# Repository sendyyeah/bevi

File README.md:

# bevi
 Inspired by Vortex Vibe and Wyvern, so here is Vibe Southpaw

## Case File

You can find acrylic sandwich case file [here](https://github.com/sendz/keyboard-case)

## License

This design may be reproduced, modified, and manufactured for **Personal Use Only** and not for **Public Sale**, however I allow to anyone who want to do small GB for their community for maximum of 10 pieces of this PCB per group buy.

)

This work is licensed under a [Creative Commons Attribution-NonCommercial 4.0 International License](http://creativecommons.org/licenses/by-nc/4.0/).

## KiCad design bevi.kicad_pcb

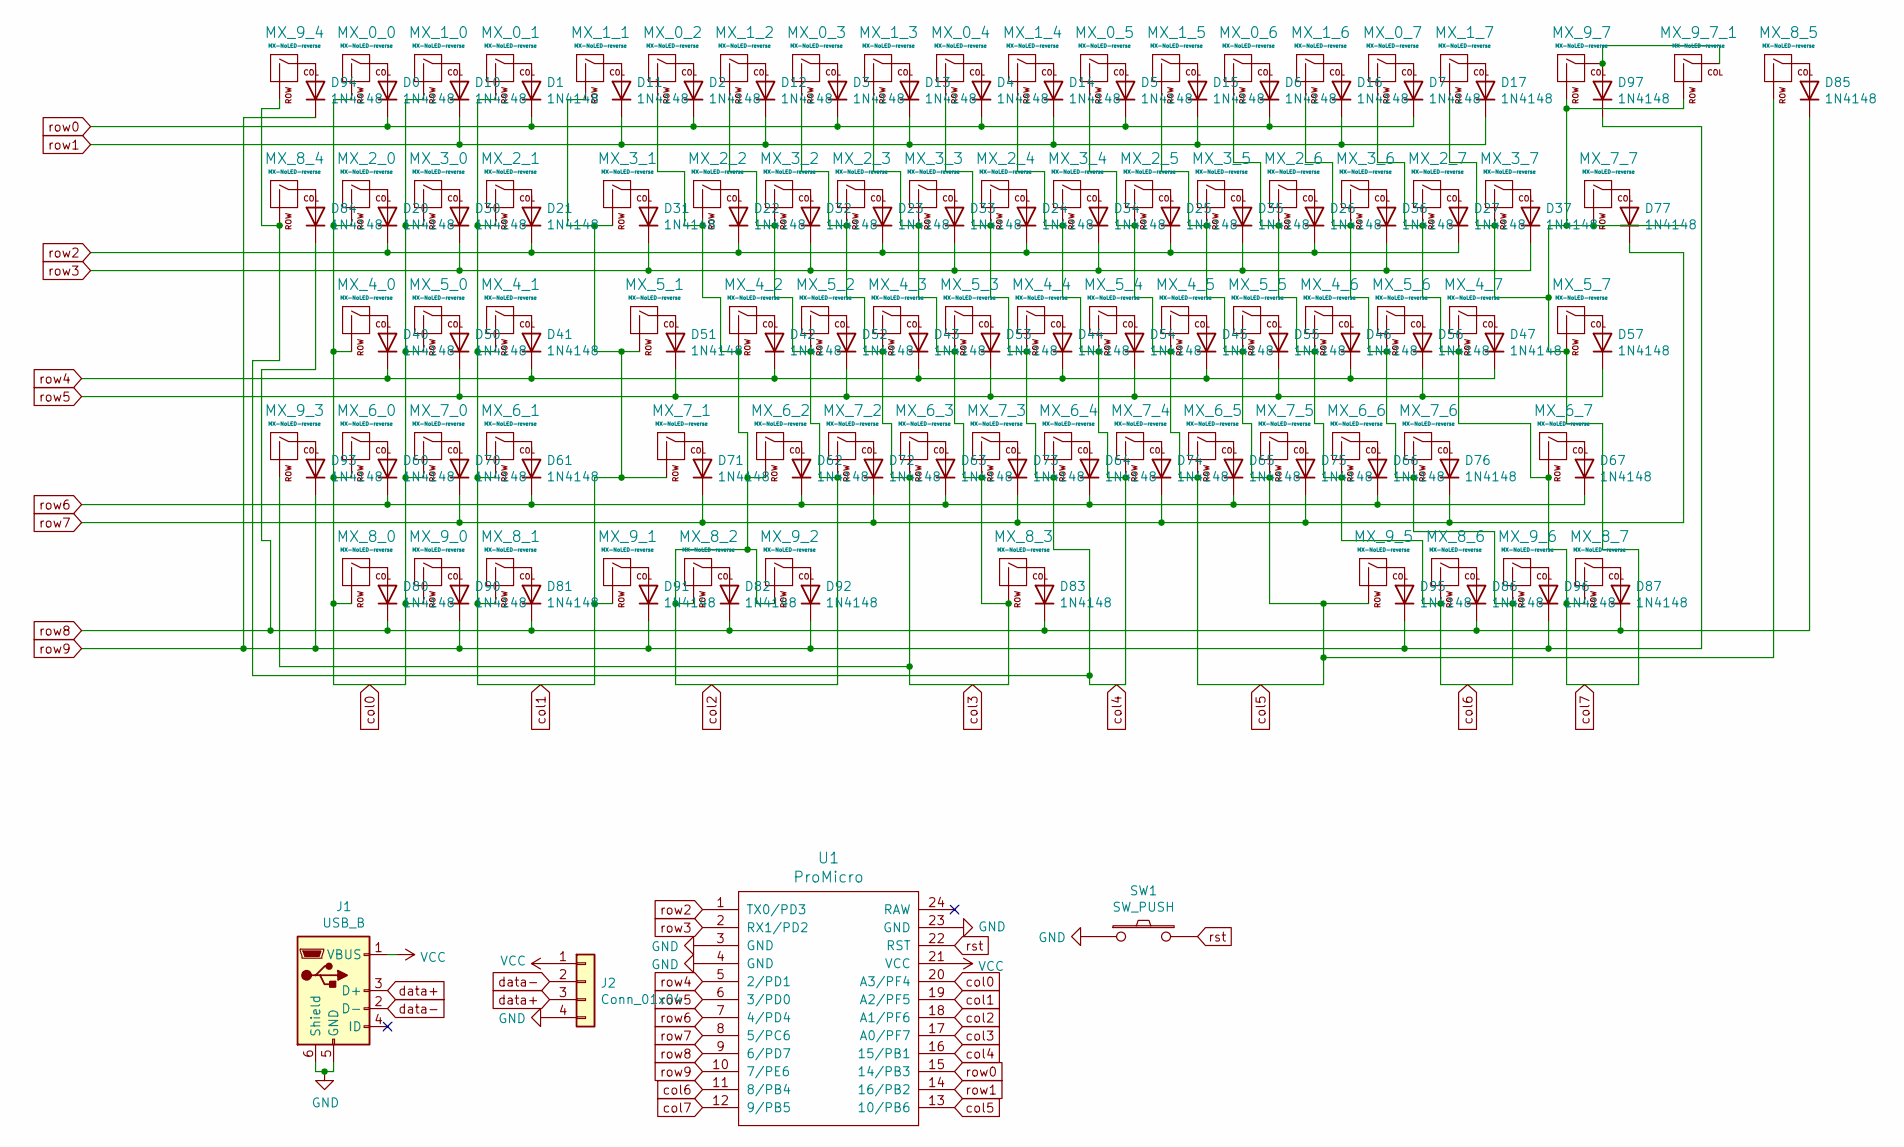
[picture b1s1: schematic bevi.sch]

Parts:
D0, D1, D2, D3, D4, D5, D6, D7, D10, D11, D12, D13, D14, D15, D16, D17, D20, D21, D22, D23, D24, D25, D26, D27, D30, D31, D32, D33, D34, D35, D36, D37, D40, D41, D42, D43, D44, D45, D46, D47, D50, D51, D52, D53, D54, D55, D56, D57, D60, D61, D62, D63, D64, D65, D66, D67, D70, D71, D72, D73, D74, D75, D76, D77, D80, D81, D82, D83, D84, D85, D86, D87, D90, D91, D92, D93, D94, D95, D96, D97: 1N4148; Diode-Hybrid-Back
J1: USB_B; USB-Mini-B_ LCSC-C46398
J2: Conn_01x04; PinHeader_1x04_P2.00mm_Vertical
MX_0_0, MX_0_1, MX_0_2, MX_0_3, MX_0_4, MX_0_5, MX_0_6, MX_0_7, MX_1_0, MX_1_1, MX_1_2, MX_1_3, MX_1_4, MX_1_5, MX_1_6, MX_1_7, MX_2_0, MX_2_1, MX_2_2, MX_2_3, MX_2_4, MX_2_5, MX_2_6, MX_2_7, MX_3_0, MX_3_2, MX_3_3, MX_3_4, MX_3_5, MX_3_6, MX_3_7, MX_4_0, MX_4_1, MX_4_2, MX_4_3, MX_4_4, MX_4_5, MX_4_6, MX_4_7, MX_5_0, MX_5_2, MX_5_3, MX_5_4, MX_5_5, MX_5_6, MX_6_0, MX_6_1, MX_6_2, MX_6_3, MX_6_4, MX_6_5, MX_6_6, MX_7_0, MX_7_2, MX_7_3, MX_7_4, MX_7_5, MX_7_6, MX_8_0, MX_8_1, MX_8_5, MX_9_0, MX_9_4, MX_9_7_1: MX-NoLED-reverse; MXOnly-1U-NoLED
MX_3_1, MX_7_7: MX-NoLED-reverse; MXOnly-1.5U-NoLED
MX_5_1: MX-NoLED-reverse; MXOnly-1.75U-NoLED
MX_5_7, MX_7_1: MX-NoLED-reverse; MXOnly-2.25U-NoLED
MX_6_7: MX-NoLED-reverse; MXOnly-2.75U-NoLED
MX_8_2, MX_8_6, MX_8_7, MX_9_1, MX_9_2, MX_9_5, MX_9_6: MX-NoLED-reverse; MXOnly-1.25U-NoLED
MX_8_3: MX-NoLED-reverse; MXOnly-6.25U-ReversedStabilizers-NoLED
MX_8_4, MX_9_3: MX-NoLED-reverse; MXOnly-2U-NoLED-Vertical
MX_9_7: MX-NoLED-reverse; MXOnly-2U-NoLED
SW1: SW_PUSH; SW_PUSH_6mm
U1: ProMicro; ArduinoProMicro-BackSide

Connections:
GND: J1.5 (GND), J1.6 (Shield), J2.4, SW1.1, U1.3 (GND), U1.4 (GND), U1.23 (GND)
unnamed: D0.2 (A), MX_0_0.1 (COL)
unnamed: D1.2 (A), MX_0_1.1 (COL)
unnamed: D2.2 (A), MX_0_2.1 (COL)
unnamed: D3.2 (A), MX_0_3.1 (COL)
unnamed: D4.2 (A), MX_0_4.1 (COL)
unnamed: D5.2 (A), MX_0_5.1 (COL)
unnamed: D6.2 (A), MX_0_6.1 (COL)
unnamed: D7.2 (A), MX_0_7.1 (COL)
unnamed: D10.2 (A), MX_1_0.1 (COL)
unnamed: D11.2 (A), MX_1_1.1 (COL)
unnamed: D12.2 (A), MX_1_2.1 (COL)
unnamed: D13.2 (A), MX_1_3.1 (COL)
unnamed: D14.2 (A), MX_1_4.1 (COL)
unnamed: D15.2 (A), MX_1_5.1 (COL)
unnamed: D16.2 (A), MX_1_6.1 (COL)
unnamed: D17.2 (A), MX_1_7.1 (COL)
unnamed: D20.2 (A), MX_2_0.1 (COL)
unnamed: D21.2 (A), MX_2_1.1 (COL)
unnamed: D22.2 (A), MX_2_2.1 (COL)
unnamed: D23.2 (A), MX_2_3.1 (COL)
unnamed: D24.2 (A), MX_2_4.1 (COL)
unnamed: D25.2 (A), MX_2_5.1 (COL)
unnamed: D26.2 (A), MX_2_6.1 (COL)
unnamed: D27.2 (A), MX_2_7.1 (COL)
unnamed: D30.2 (A), MX_3_0.1 (COL)
unnamed: D31.2 (A), MX_3_1.1 (COL)
unnamed: D32.2 (A), MX_3_2.1 (COL)
unnamed: D33.2 (A), MX_3_3.1 (COL)
unnamed: D34.2 (A), MX_3_4.1 (COL)
unnamed: D35.2 (A), MX_3_5.1 (COL)
unnamed: D36.2 (A), MX_3_6.1 (COL)
unnamed: D37.2 (A), MX_3_7.1 (COL)
unnamed: D40.2 (A), MX_4_0.1 (COL)
unnamed: D41.2 (A), MX_4_1.1 (COL)
unnamed: D42.2 (A), MX_4_2.1 (COL)
unnamed: D43.2 (A), MX_4_3.1 (COL)
unnamed: D44.2 (A), MX_4_4.1 (COL)
unnamed: D45.2 (A), MX_4_5.1 (COL)
unnamed: D46.2 (A), MX_4_6.1 (COL)
unnamed: D47.2 (A), MX_4_7.1 (COL)
unnamed: D50.2 (A), MX_5_0.1 (COL)
unnamed: D51.2 (A), MX_5_1.1 (COL)
unnamed: D52.2 (A), MX_5_2.1 (COL)
unnamed: D53.2 (A), MX_5_3.1 (COL)
unnamed: D54.2 (A), MX_5_4.1 (COL)
unnamed: D55.2 (A), MX_5_5.1 (COL)
unnamed: D56.2 (A), MX_5_6.1 (COL)
unnamed: D57.2 (A), MX_5_7.1 (COL)
unnamed: D60.2 (A), MX_6_0.1 (COL)
unnamed: D61.2 (A), MX_6_1.1 (COL)
unnamed: D62.2 (A), MX_6_2.1 (COL)
unnamed: D63.2 (A), MX_6_3.1 (COL)
unnamed: D64.2 (A), MX_6_4.1 (COL)
unnamed: D65.2 (A), MX_6_5.1 (COL)
unnamed: D66.2 (A), MX_6_6.1 (COL)
unnamed: D67.2 (A), MX_6_7.1 (COL)
unnamed: D70.2 (A), MX_7_0.1 (COL)
unnamed: D71.2 (A), MX_7_1.1 (COL)
unnamed: D72.2 (A), MX_7_2.1 (COL)
unnamed: D73.2 (A), MX_7_3.1 (COL)
unnamed: D74.2 (A), MX_7_4.1 (COL)
unnamed: D75.2 (A), MX_7_5.1 (COL)
unnamed: D76.2 (A), MX_7_6.1 (COL)
unnamed: D77.2 (A), MX_7_7.1 (COL)
unnamed: D80.2 (A), MX_8_0.1 (COL)
unnamed: D81.2 (A), MX_8_1.1 (COL)
unnamed: D82.2 (A), MX_8_2.1 (COL)
unnamed: D83.2 (A), MX_8_3.1 (COL)
unnamed: D84.2 (A), MX_8_4.1 (COL)
unnamed: D85.2 (A), MX_8_5.1 (COL)
unnamed: D86.2 (A), MX_8_6.1 (COL)
unnamed: D87.2 (A), MX_8_7.1 (COL)
unnamed: D90.2 (A), MX_9_0.1 (COL)
unnamed: D91.2 (A), MX_9_1.1 (COL)
unnamed: D92.2 (A), MX_9_2.1 (COL)
unnamed: D93.2 (A), MX_9_3.1 (COL)
unnamed: D94.2 (A), MX_9_4.1 (COL)
unnamed: D95.2 (A), MX_9_5.1 (COL)
unnamed: D96.2 (A), MX_9_6.1 (COL)
unnamed: D97.2 (A), MX_9_7.1 (COL), MX_9_7_1.1 (COL)
VCC: J1.1 (VBUS), J2.1, U1.21 (VCC)
col0: MX_0_0.2 (ROW), MX_1_0.2 (ROW), MX_2_0.2 (ROW), MX_3_0.2 (ROW), MX_4_0.2 (ROW), MX_5_0.2 (ROW), MX_6_0.2 (ROW), MX_7_0.2 (ROW), MX_8_0.2 (ROW), MX_9_0.2 (ROW), U1.20 (A3/PF4)
col1: MX_0_1.2 (ROW), MX_1_1.2 (ROW), MX_2_1.2 (ROW), MX_3_1.2 (ROW), MX_4_1.2 (ROW), MX_5_1.2 (ROW), MX_6_1.2 (ROW), MX_7_1.2 (ROW), MX_8_1.2 (ROW), MX_9_1.2 (ROW), U1.19 (A2/PF5)
col2: MX_0_2.2 (ROW), MX_1_2.2 (ROW), MX_2_2.2 (ROW), MX_3_2.2 (ROW), MX_4_2.2 (ROW), MX_5_2.2 (ROW), MX_6_2.2 (ROW), MX_7_2.2 (ROW), MX_8_2.2 (ROW), MX_9_2.2 (ROW), U1.18 (A1/PF6)
col3: MX_0_3.2 (ROW), MX_1_3.2 (ROW), MX_2_3.2 (ROW), MX_3_3.2 (ROW), MX_4_3.2 (ROW), MX_5_3.2 (ROW), MX_6_3.2 (ROW), MX_7_3.2 (ROW), MX_8_3.2 (ROW), MX_9_3.2 (ROW), U1.17 (A0/PF7)
col4: MX_0_4.2 (ROW), MX_1_4.2 (ROW), MX_2_4.2 (ROW), MX_3_4.2 (ROW), MX_4_4.2 (ROW), MX_5_4.2 (ROW), MX_6_4.2 (ROW), MX_7_4.2 (ROW), MX_8_4.2 (ROW), MX_9_4.2 (ROW), U1.16 (15/PB1)
col5: MX_0_5.2 (ROW), MX_1_5.2 (ROW), MX_2_5.2 (ROW), MX_3_5.2 (ROW), MX_4_5.2 (ROW), MX_5_5.2 (ROW), MX_6_5.2 (ROW), MX_7_5.2 (ROW), MX_8_5.2 (ROW), MX_9_5.2 (ROW), U1.13 (10/PB6)
col6: MX_0_6.2 (ROW), MX_1_6.2 (ROW), MX_2_6.2 (ROW), MX_3_6.2 (ROW), MX_4_6.2 (ROW), MX_5_6.2 (ROW), MX_6_6.2 (ROW), MX_7_6.2 (ROW), MX_8_6.2 (ROW), MX_9_6.2 (ROW), U1.11 (8/PB4)
col7: MX_0_7.2 (ROW), MX_1_7.2 (ROW), MX_2_7.2 (ROW), MX_3_7.2 (ROW), MX_4_7.2 (ROW), MX_5_7.2 (ROW), MX_6_7.2 (ROW), MX_7_7.2 (ROW), MX_8_7.2 (ROW), MX_9_7.2 (ROW), MX_9_7_1.2 (ROW), U1.12 (9/PB5)
data+: J1.3 (D+), J2.3
data-: J1.2 (D-), J2.2
row0: D0.1 (K), D1.1 (K), D2.1 (K), D3.1 (K), D4.1 (K), D5.1 (K), D6.1 (K), D7.1 (K), U1.15 (14/PB3)
row1: D10.1 (K), D11.1 (K), D12.1 (K), D13.1 (K), D14.1 (K), D15.1 (K), D16.1 (K), D17.1 (K), U1.14 (16/PB2)
row2: D20.1 (K), D21.1 (K), D22.1 (K), D23.1 (K), D24.1 (K), D25.1 (K), D26.1 (K), D27.1 (K), U1.1 (TX0/PD3)
row3: D30.1 (K), D31.1 (K), D32.1 (K), D33.1 (K), D34.1 (K), D35.1 (K), D36.1 (K), D37.1 (K), U1.2 (RX1/PD2)
row4: D40.1 (K), D41.1 (K), D42.1 (K), D43.1 (K), D44.1 (K), D45.1 (K), D46.1 (K), D47.1 (K), U1.5 (2/PD1)
row5: D50.1 (K), D51.1 (K), D52.1 (K), D53.1 (K), D54.1 (K), D55.1 (K), D56.1 (K), D57.1 (K), U1.6 (3/PD0)
row6: D60.1 (K), D61.1 (K), D62.1 (K), D63.1 (K), D64.1 (K), D65.1 (K), D66.1 (K), D67.1 (K), U1.7 (4/PD4)
row7: D70.1 (K), D71.1 (K), D72.1 (K), D73.1 (K), D74.1 (K), D75.1 (K), D76.1 (K), D77.1 (K), U1.8 (5/PC6)
row8: D80.1 (K), D81.1 (K), D82.1 (K), D83.1 (K), D84.1 (K), D85.1 (K), D86.1 (K), D87.1 (K), U1.9 (6/PD7)
row9: D90.1 (K), D91.1 (K), D92.1 (K), D93.1 (K), D94.1 (K), D95.1 (K), D96.1 (K), D97.1 (K), U1.10 (7/PE6)
rst: SW1.2, U1.22 (RST)

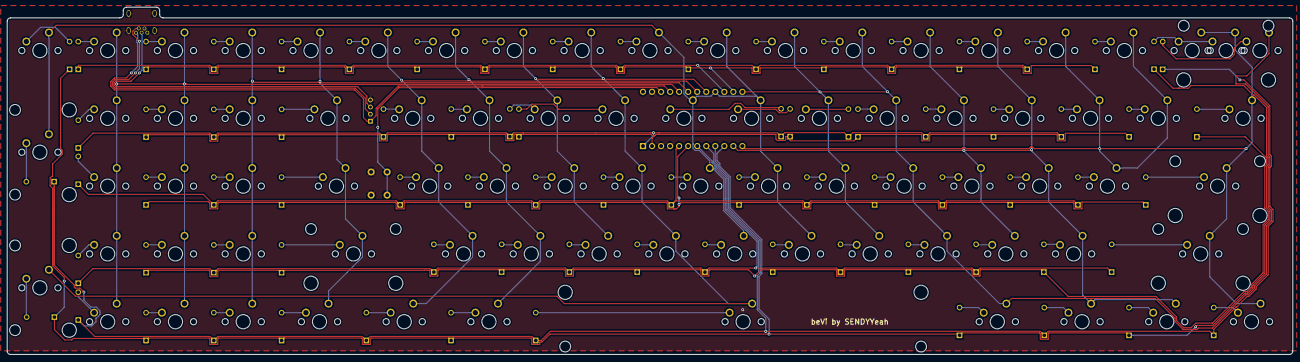
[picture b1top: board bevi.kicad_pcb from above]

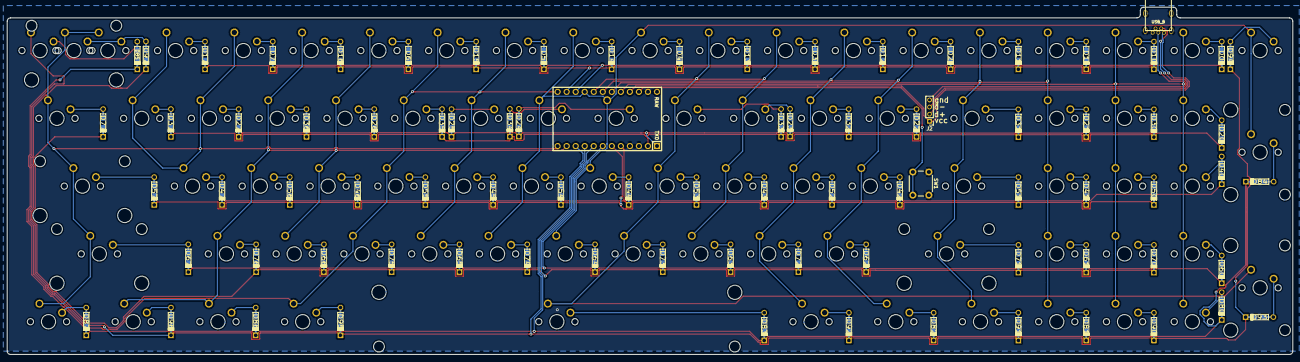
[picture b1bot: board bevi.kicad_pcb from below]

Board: 2 copper layers, 361.3 x 97.6 mm, 165 parts (3 on the bottom side), 103 nets.

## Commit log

2021-02-06 Remove gerbers file
2021-02-10 Update diodes position
2021-02-26 Add firmwares
2021-02-26 Add case design
2021-03-03 Add case file link
2021-03-03 Move diodes
2021-03-05 Update Diode Layout
